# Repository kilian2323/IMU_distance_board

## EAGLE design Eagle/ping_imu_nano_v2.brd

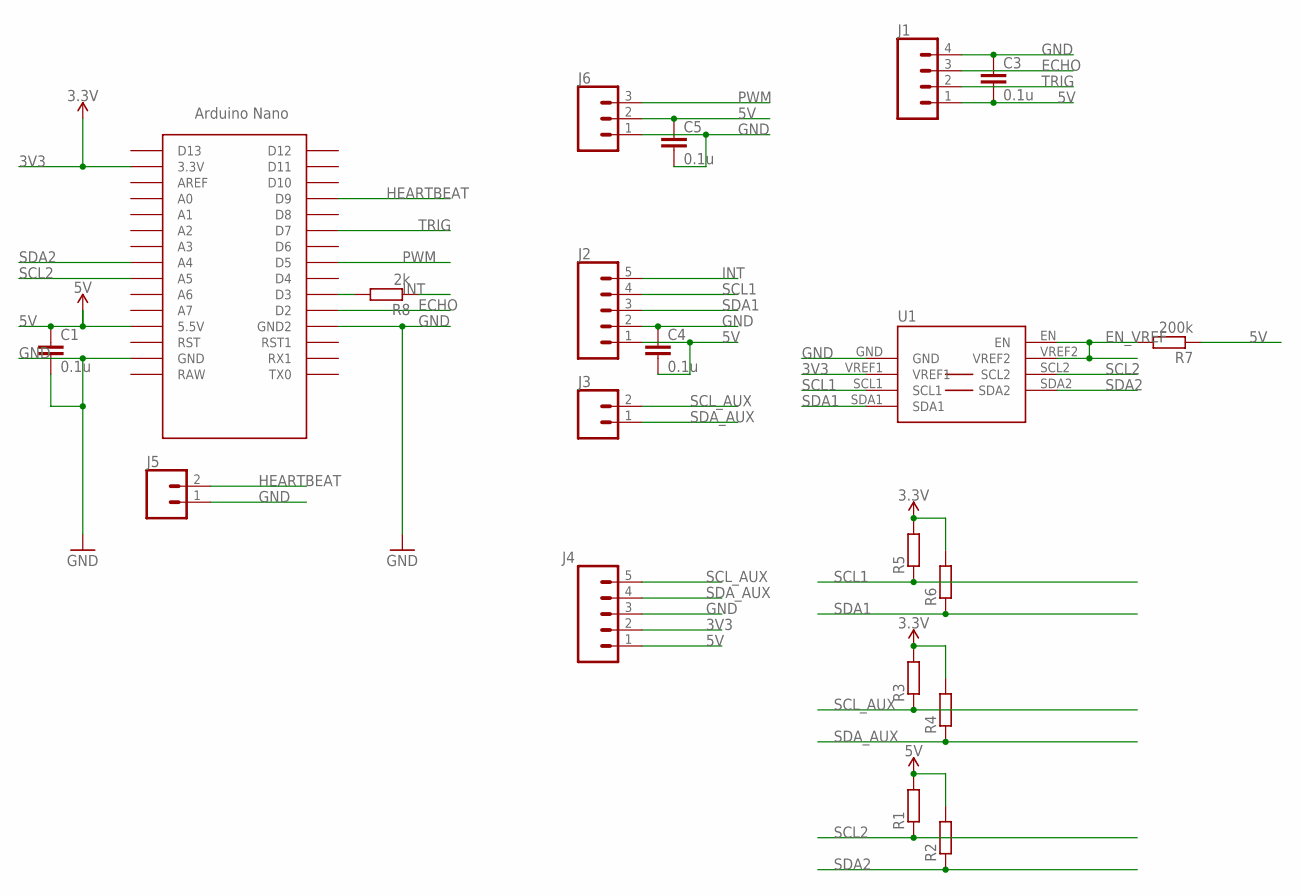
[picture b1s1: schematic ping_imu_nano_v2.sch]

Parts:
C1, C3, C4, C5: 0.1u; C1206
J1: CONN_04LONGPADS; 1X04_LONGPADS
J2, J4: CONN_05PTH_LONGPADS; 1X05_LONGPADS
J3, J5: CONN_02PTH3; 1X02_LONGPADS
J6: CONN_03LONGPADS; 1X03_LONGPADS
R1, R2, R3, R4, R5, R6: R-EU_M1206; M1206
R7: 200k; M1206
R8: 2k; M1206
U1: PCA9306SO8; SO8
U$1: NANO_BARE

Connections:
3V3: J4.2, R3.2, R4.2, R5.2, R6.2, U1.VREF1, U$1.3.3V
5V: C1.1, C3.2, C4.2, C5.1, J1.1, J2.1, J4.1, J6.2, R1.2, R2.2, R7.1, U$1.5V (5.5V)
ECHO: J1.3, U$1.D2
EN_VREF: R7.2, U1.EN, U1.VREF2
GND: C1.2, C3.1, C4.1, C5.2, J1.4, J2.2, J4.3, J5.1, J6.1, U1.GND, U$1.GND, U$1.GND1 (GND2)
HEARTBEAT: J5.2, U$1.D9
INT: J2.5, R8.1
unnamed: R8.2, U$1.D3
PWM: J6.3, U$1.D5
SCL1: J2.4, R5.1, U1.SCL1
SCL2: R1.1, U1.SCL2, U$1.A5
SCL_AUX: J3.2, J4.5, R3.1
SDA1: J2.3, R6.1, U1.SDA1
SDA2: R2.1, U1.SDA2, U$1.A4
SDA_AUX: J3.1, J4.4, R4.1
TRIG: J1.2, U$1.D7

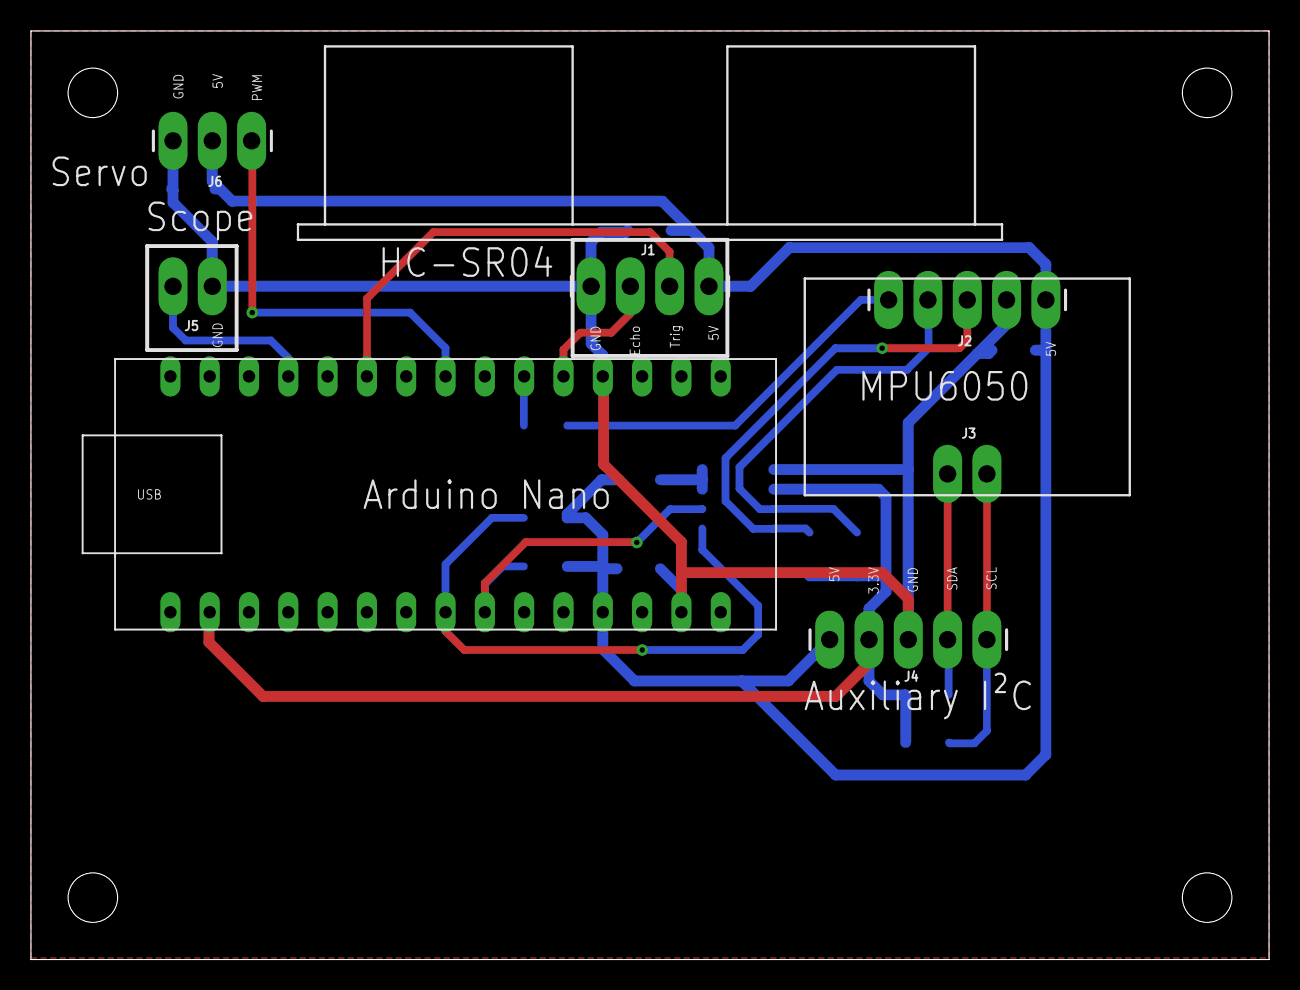
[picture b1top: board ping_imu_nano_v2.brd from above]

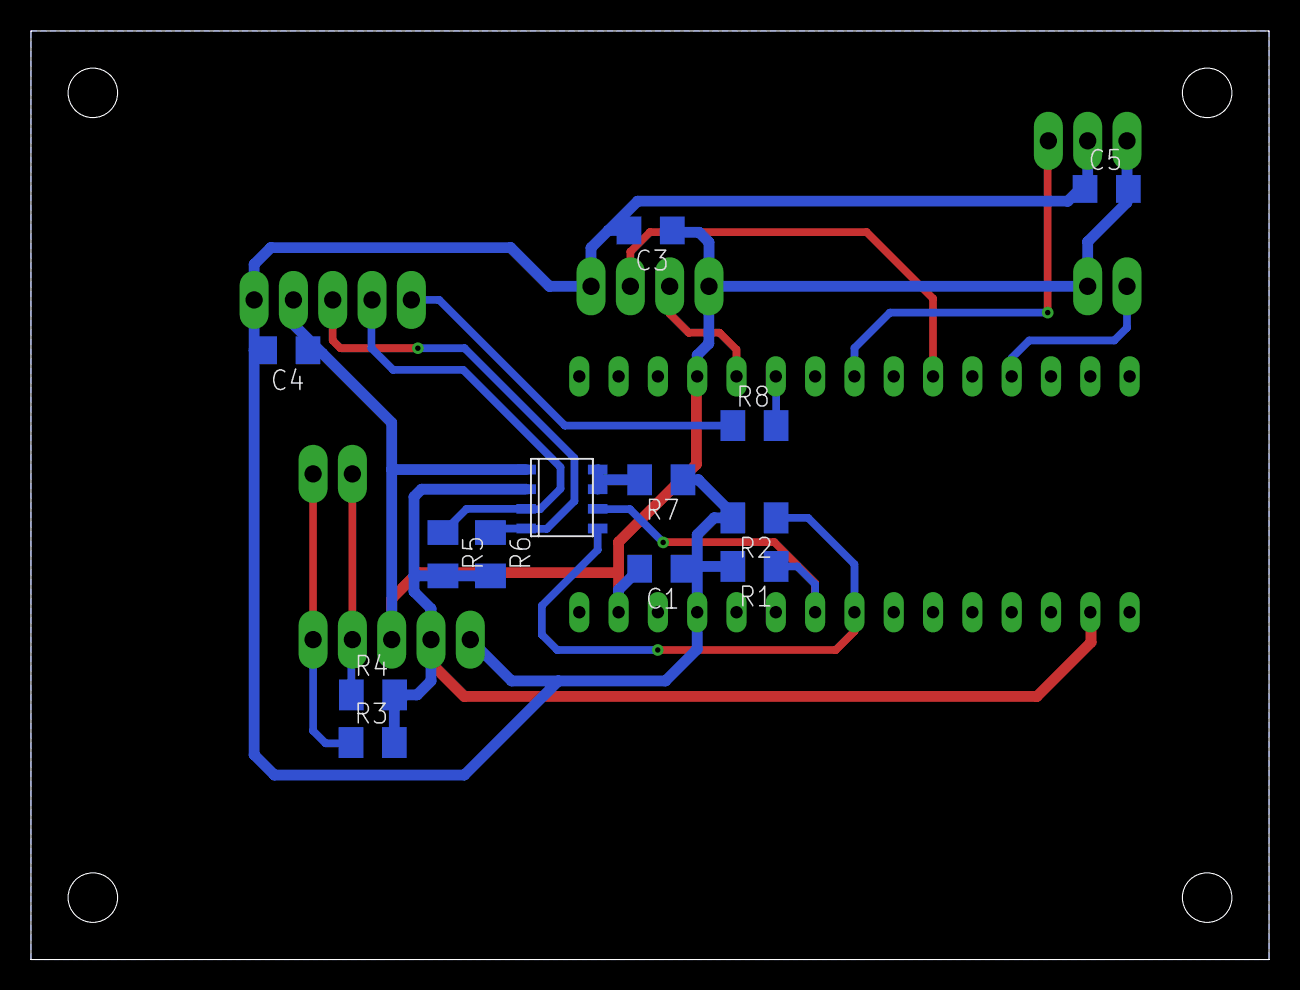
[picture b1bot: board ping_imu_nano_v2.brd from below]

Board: 2 copper layers, 80.0 x 60.0 mm, 20 parts (13 on the bottom side), 16 nets.

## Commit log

2021-02-02 Initial commit.

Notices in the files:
parts and their libraries:
SparkFun-Connectors: Licensing: Creative Commons ShareAlike 4.0 International - https://creativecommons.org/licenses/by-sa/4.0
